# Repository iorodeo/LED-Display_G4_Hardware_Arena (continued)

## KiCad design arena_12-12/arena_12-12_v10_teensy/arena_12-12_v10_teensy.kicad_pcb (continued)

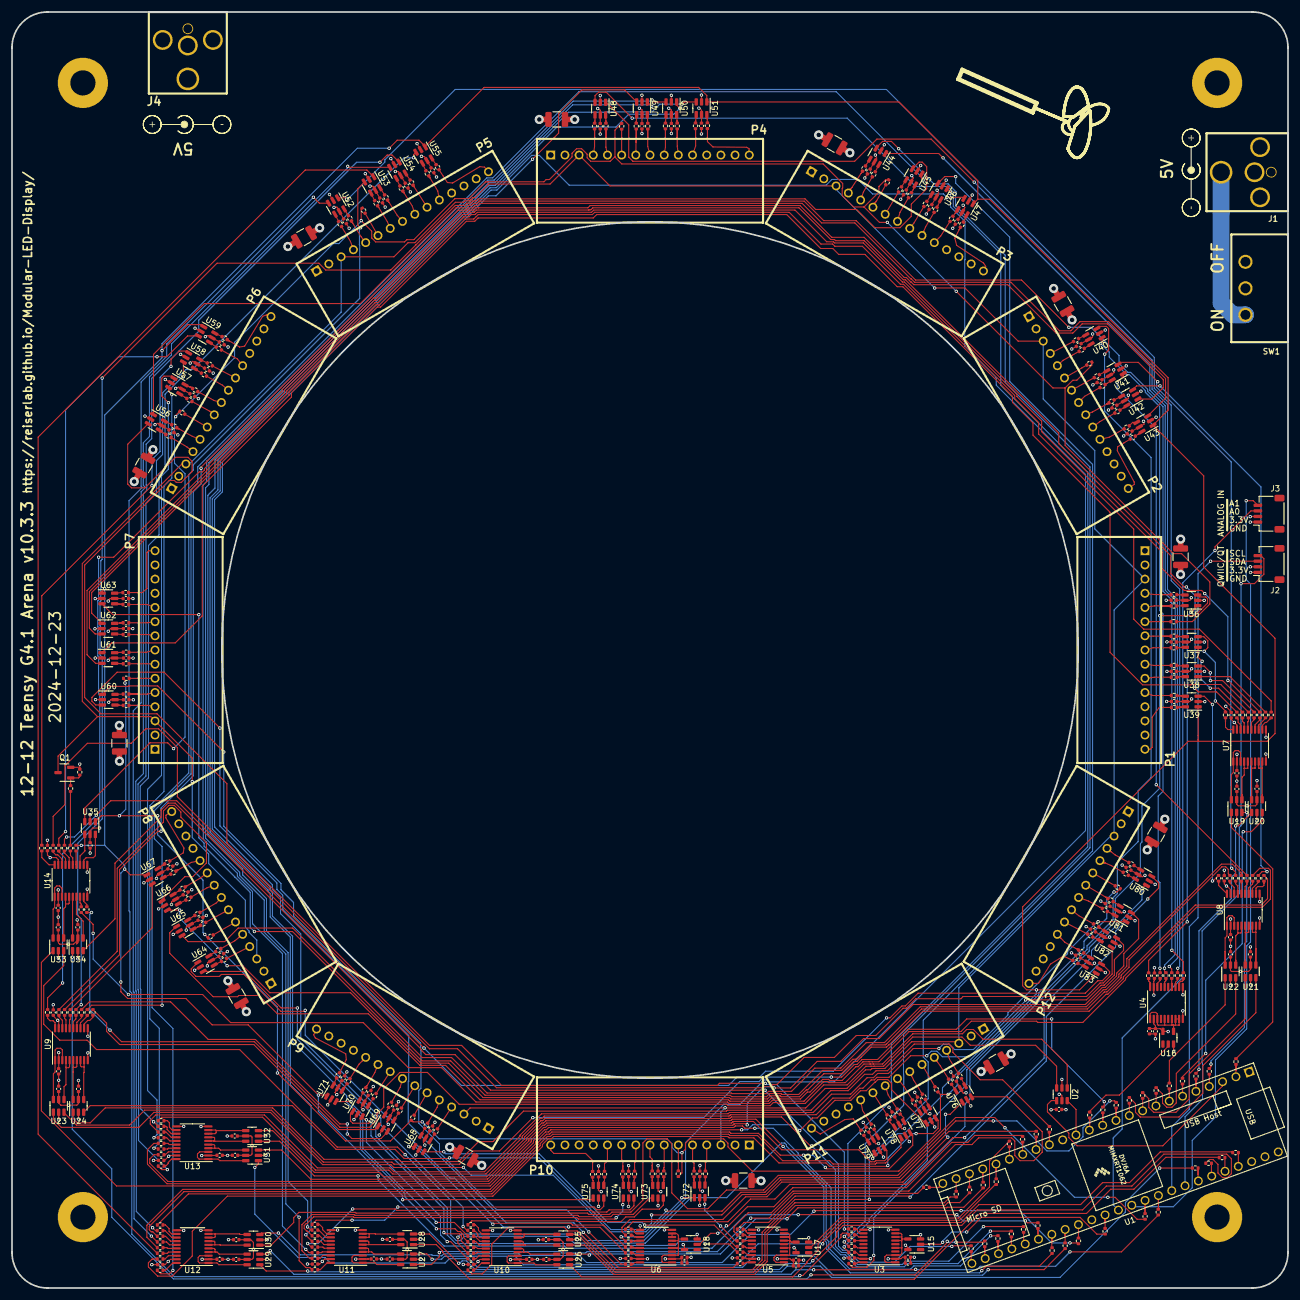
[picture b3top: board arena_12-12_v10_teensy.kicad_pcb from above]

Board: 6 copper layers, 228.6 x 228.6 mm, 445 parts (0 on the bottom side), 504 nets.

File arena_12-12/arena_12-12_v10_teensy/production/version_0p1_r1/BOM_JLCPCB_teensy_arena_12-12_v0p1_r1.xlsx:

Comment | Designator | Footprint | LCSC Part #（optional） | Qty
33 Ohm resistor | R215,R62,R48,R75,R201,R173,R177,R222,R214,R147,R10,R212,R203,R168,R139,R91,R86,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 | 0402 | C25105 | 232
0.1uF ceramic capacitor | C30,C67,C69,C48,C91,C5,C61,C26,C19,C39,C40,C76,C73,C2,C93,C60,C50,C25,C15,C46,C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 | 0402 | C1525 | 94
SN74LVC2G17DBVR dual Schmitt-trigger buffer | U36,U60,U33,U45,U20,U28,U2,U48,U38,U79,U62,U37,U63,U49,U26,U70,U76,U56,U53,U69,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 | SOT-23-6 | C10429 | 66
MOSFET N-channel | Q1 | SOT-23-3 | C165220 | 1
100uF ceramic capacitor | C97,C98,C106,C102,C99,C105,C95,C96,C100,C104,C103,C101 | 1210 | C7432790 | 12
Level shifter TXB0108PWR | U13,U6,U10,U3,U14,U4,U7,U12,U8,U9,U11,U5 | TSSOP-20 | C53406 | 12
4-Pin Connector, JST SM04B-SRSS-TB or similar | J2 ,J3 | SMD,P=1mm | C145956 | 2
SN74LVC1G17DBVR single schmitt trigger buffer | U17,U16,U15,U18 | SOT-23-5 | C7836 | 4
200 Ohm resistor | R1 | 0402 | C25087 | 1
20k Ohms resistor | R2 | 0402 | C25765 | 1
15x1 female header, 0.1in pitch | P10,P12,P7,P9,P11,P5,P4,P1,P6,P8,P2,P3 | through hole | global parts | 12
Slide Switch SPDT | SW1 | through hole | global parts | 1
DC Power Barrel Jack | J1, J4 | through hole | global parts | 2
Teensy4.1 | U1 | through hole | global parts | 1

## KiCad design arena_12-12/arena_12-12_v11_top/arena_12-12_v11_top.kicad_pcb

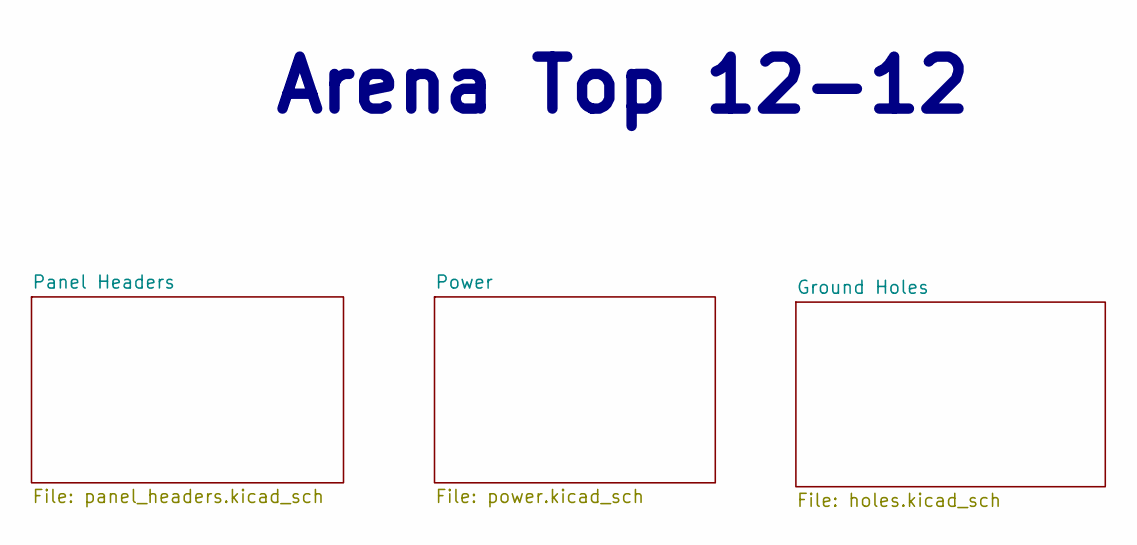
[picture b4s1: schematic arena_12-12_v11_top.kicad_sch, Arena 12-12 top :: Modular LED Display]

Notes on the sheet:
Arena Top 12-12

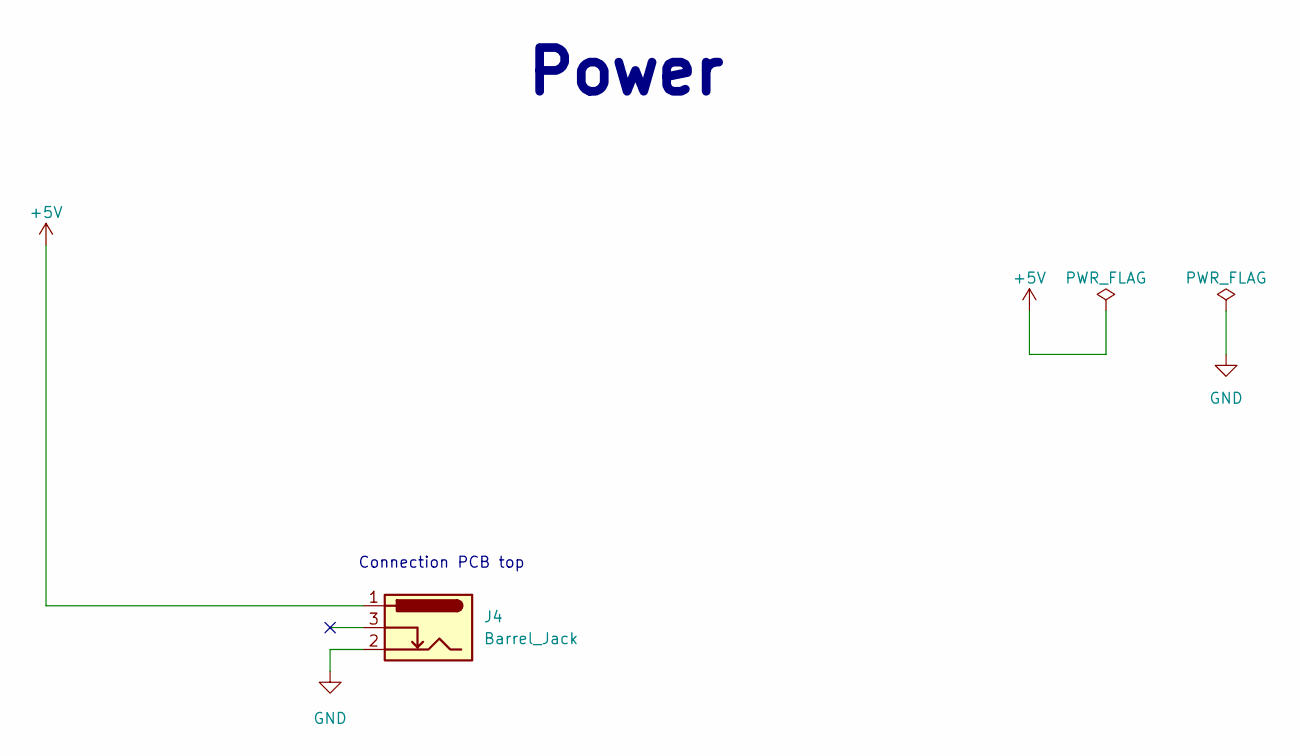
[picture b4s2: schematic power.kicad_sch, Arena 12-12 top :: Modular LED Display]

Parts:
J4: Barrel_Jack; BarrelJack_CUI_PJ-036AH-SMT_Horizontal; MPN PJ-036AH-SMT-TR; DigiKey PN CP-036AHPJTR-ND

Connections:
+5V: J4.1; also elsewhere on the board
GND: J4.2; also elsewhere on the board

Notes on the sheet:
Connection PCB top
Power

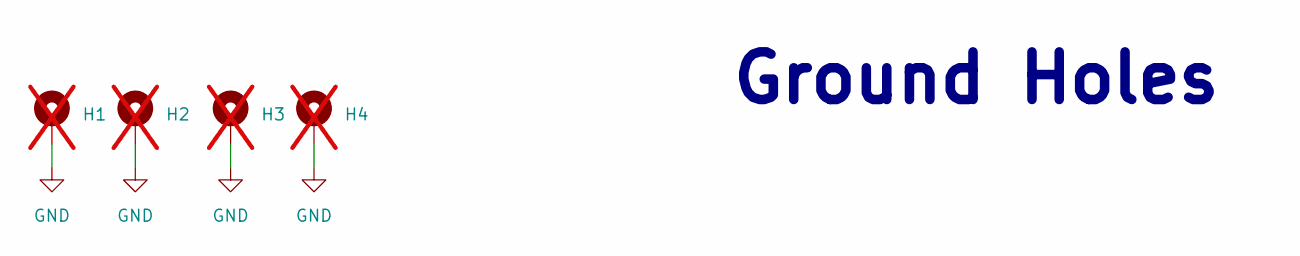
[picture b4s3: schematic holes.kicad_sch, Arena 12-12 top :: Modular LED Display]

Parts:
H1, H2, H3, H4: MountingHole_Pad; MountingHole_4.5mm_Pad; not fitted

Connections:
GND: H1.1, H2.1, H3.1, H4.1; also elsewhere on the board

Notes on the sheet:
Ground Holes

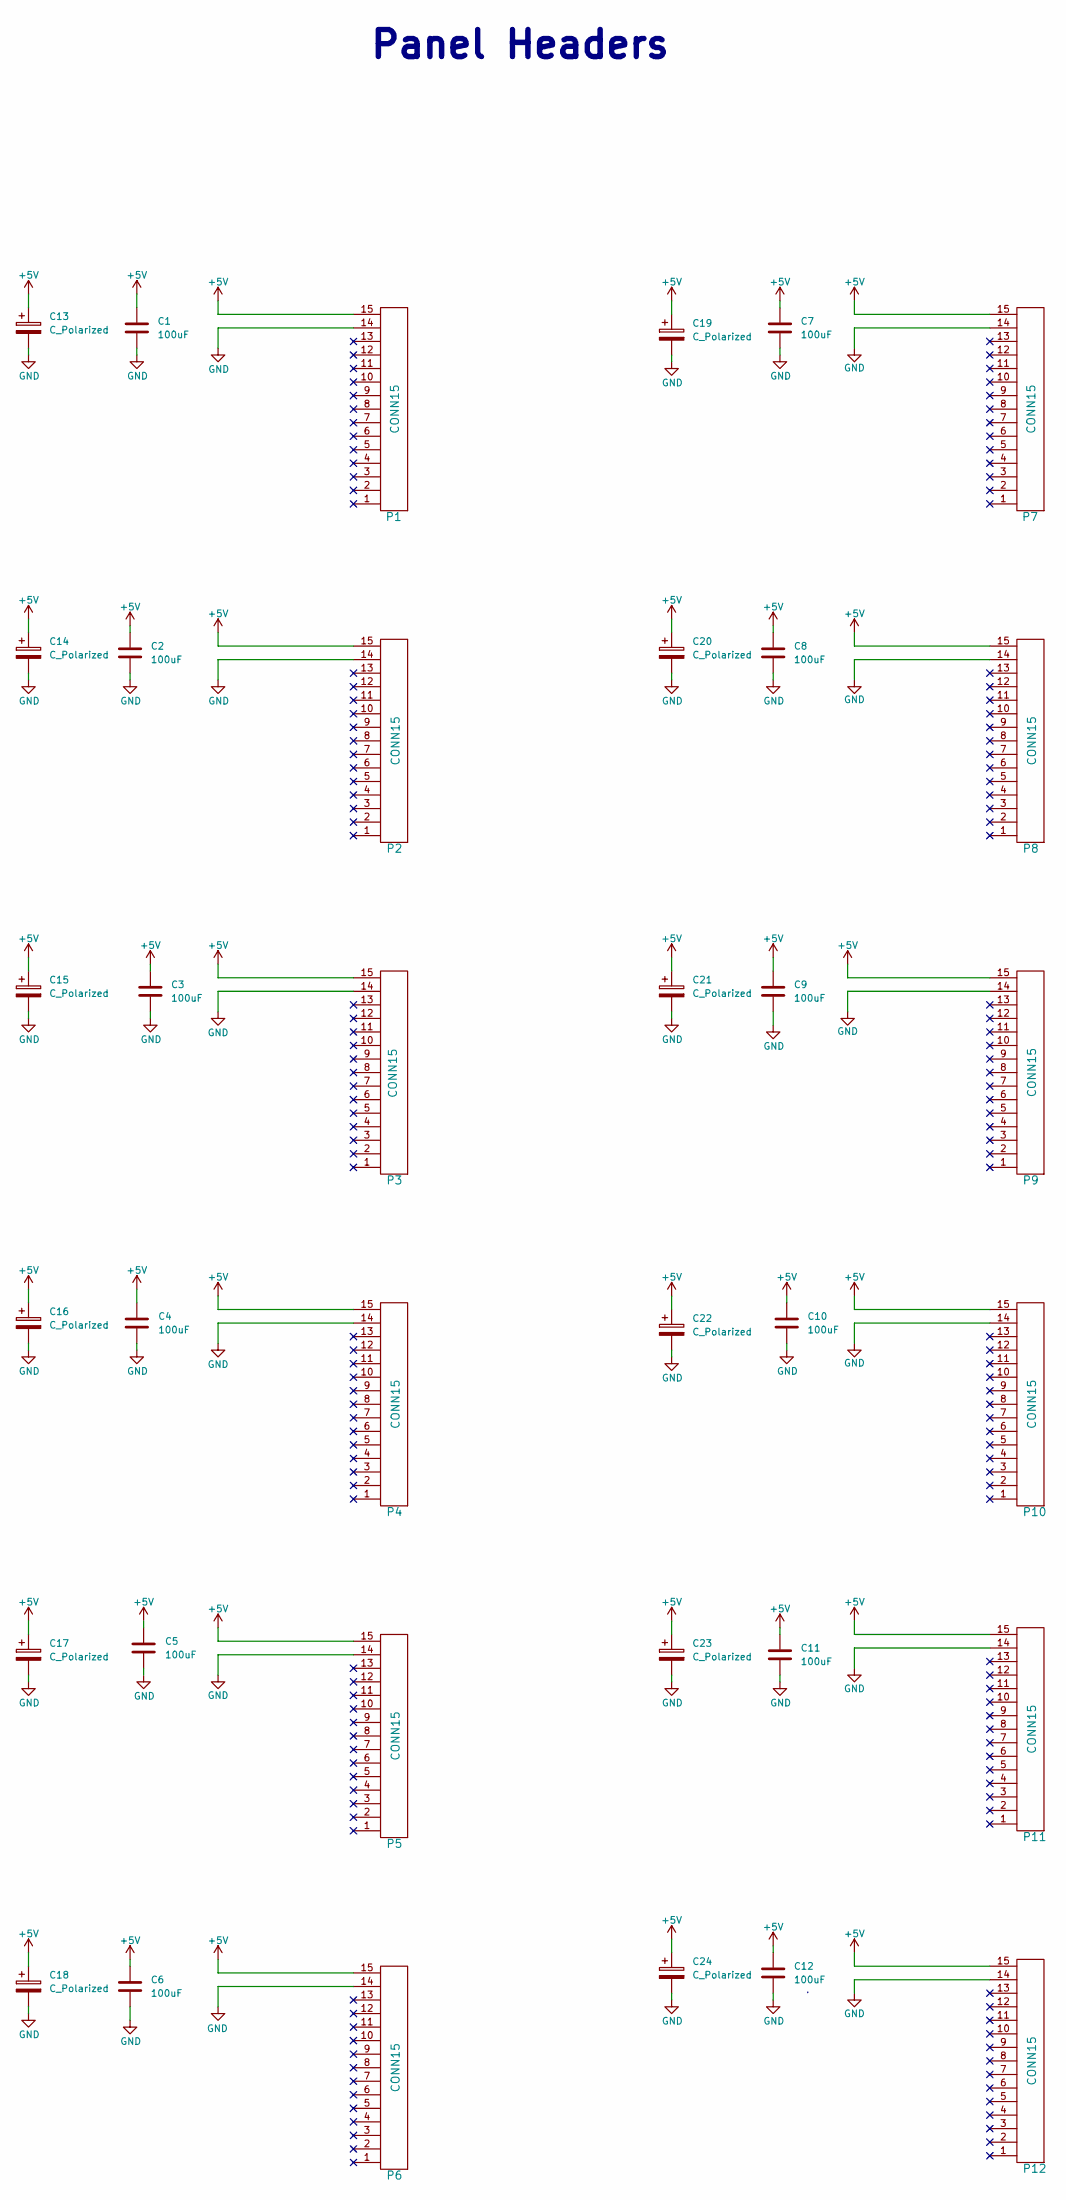
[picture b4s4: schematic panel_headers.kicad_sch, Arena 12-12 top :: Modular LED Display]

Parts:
C1, C2, C3, C4, C5, C6, C7, C8, C9, C10, C11, C12: 100uF; C_1210_3225Metric; MPN HGC1210R5107M160NSVK; LCSC Part # C7432790
C13, C14, C15, C16, C17, C18, C19, C20, C21, C22, C23, C24: C_Polarized; CP_Elec_6.3x7.7; MPN EEEFTH101XAP; DigiKey PN PCE5024TR-ND
P1, P2, P3, P4, P5, P6, P7, P8, P9, P10, P11, P12: CONN15; HEADER_TOP; MPN PRPC040SAAN-RC; DigiKey PN S1011EC-40-ND

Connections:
+5V: C1.1, C2.1, C3.1, C4.1, C5.1, C6.1, C7.1, C8.1, C9.1, C10.1, C11.1, C12.1, C13.1, C14.1, C15.1, C16.1, C17.1, C18.1, C19.1, C20.1, C21.1, C22.1, C23.1, C24.1, P1.15, P2.15, P3.15, P4.15, P5.15, P6.15, P7.15, P8.15, P9.15, P10.15, P11.15, P12.15; also elsewhere on the board
GND: C1.2, C2.2, C3.2, C4.2, C5.2, C6.2, C7.2, C8.2, C9.2, C10.2, C11.2, C12.2, C13.2, C14.2, C15.2, C16.2, C17.2, C18.2, C19.2, C20.2, C21.2, C22.2, C23.2, C24.2, P1.14, P2.14, P3.14, P4.14, P5.14, P6.14, P7.14, P8.14, P9.14, P10.14, P11.14, P12.14; also elsewhere on the board

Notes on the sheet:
Panel Headers

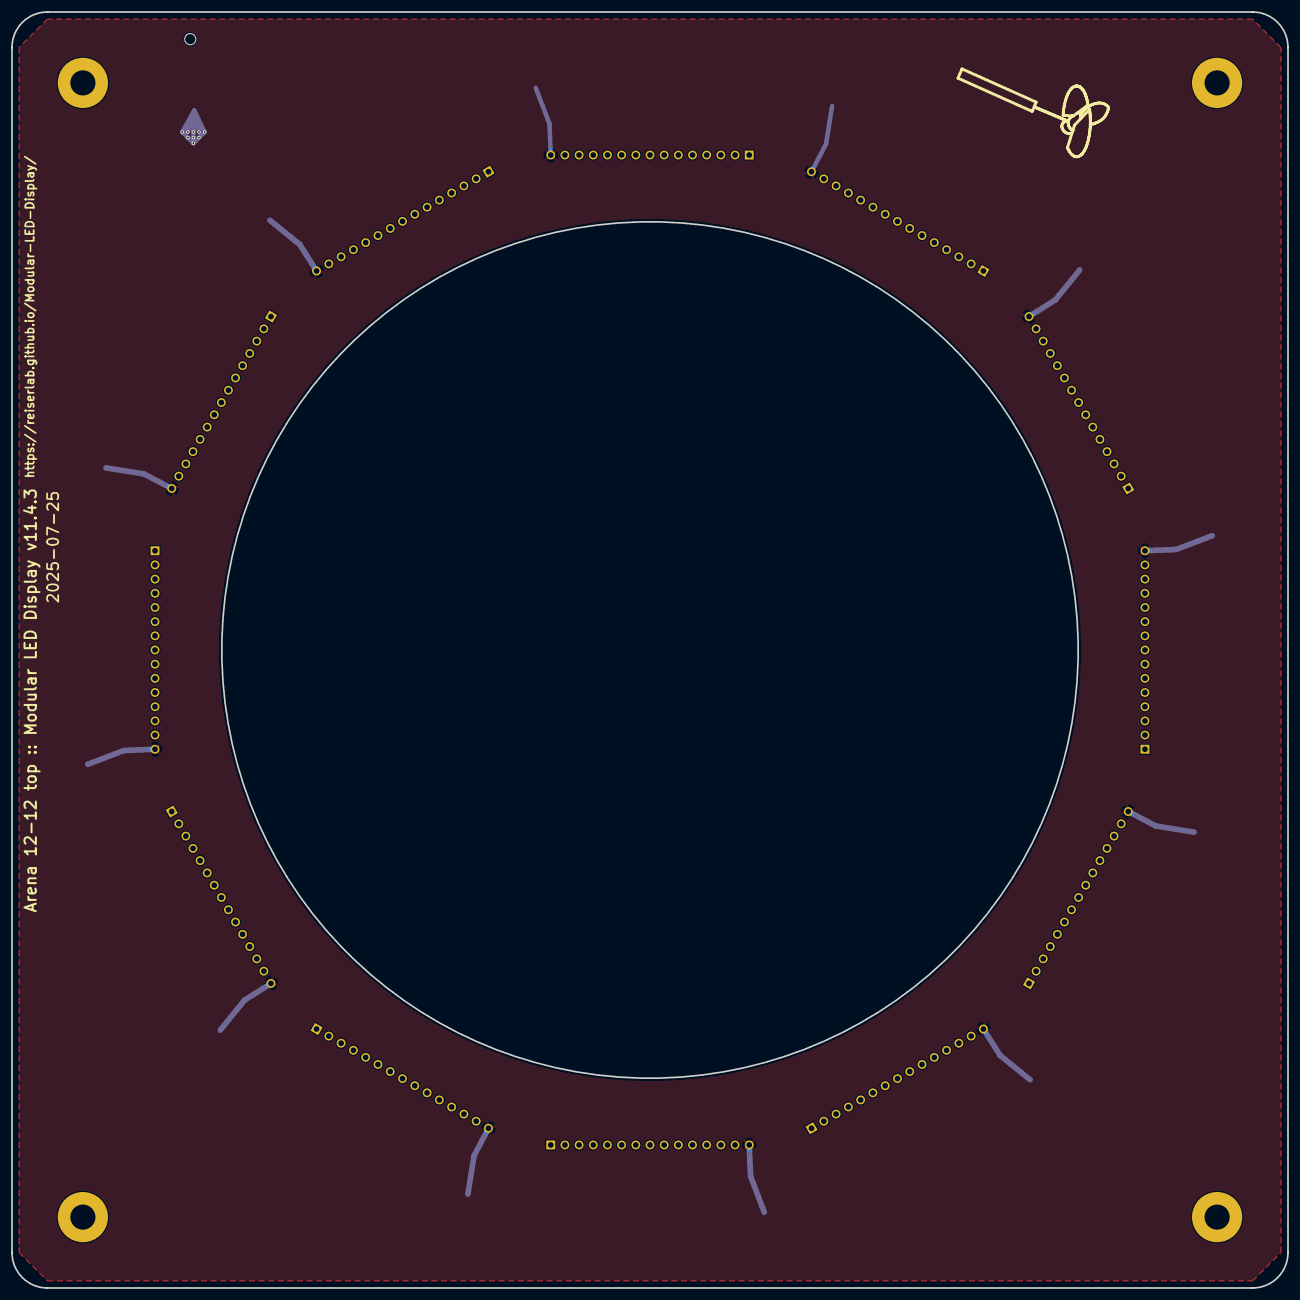
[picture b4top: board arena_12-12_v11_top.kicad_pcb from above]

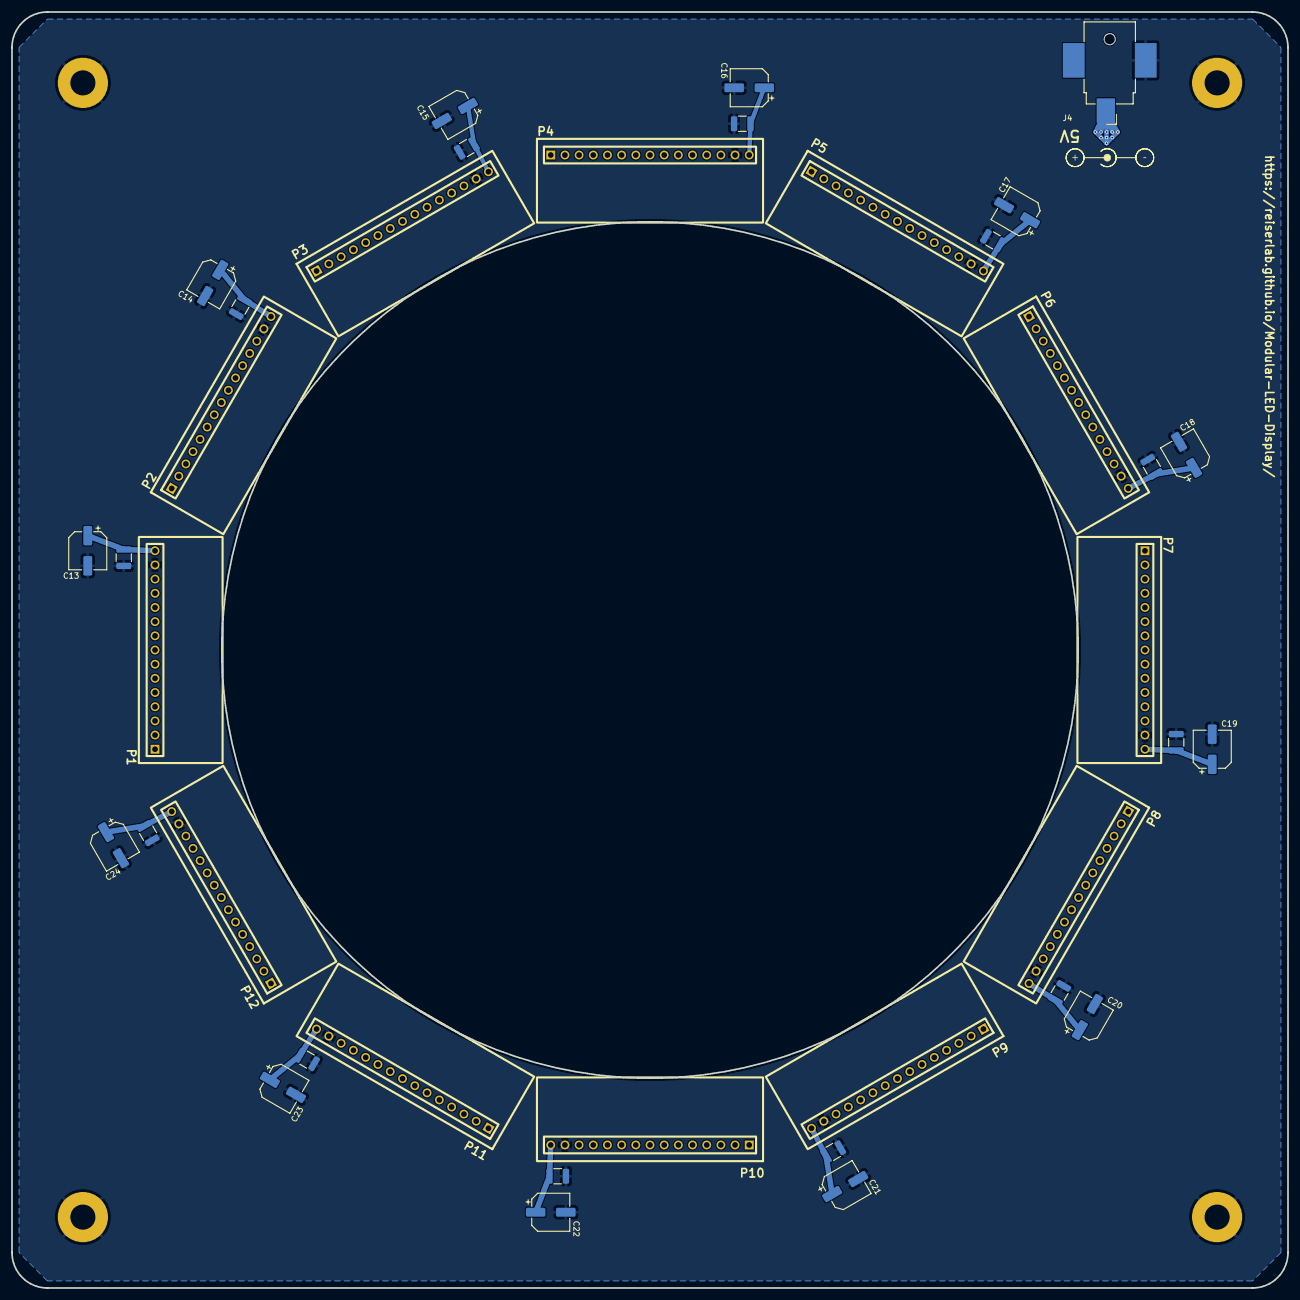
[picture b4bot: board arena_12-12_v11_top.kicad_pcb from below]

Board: 2 copper layers, 228.6 x 228.6 mm, 41 parts (37 on the bottom side), 2 nets.

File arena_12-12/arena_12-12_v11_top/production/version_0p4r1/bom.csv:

Designator,Footprint,Quantity,Value,LCSC Part #
"C1, C10, C11, C12, C2, C3, C4, C5, C6, C7, C8, C9",1210,12,100uF,C7432790
"C13, C14, C15, C16, C17, C18, C19, C20, C21, C22, C23, C24",CP_Elec_6.3x7.7,12,C_Polarized,C165974
J4,DCJACK_2PIN_HIGHCURRENT,1,Barrel_Jack,C2928097
"P1, P10, P11, P12, P2, P3, P4, P5, P6, P7, P8, P9",HEADER_TOP,12,CONN15,C7501269

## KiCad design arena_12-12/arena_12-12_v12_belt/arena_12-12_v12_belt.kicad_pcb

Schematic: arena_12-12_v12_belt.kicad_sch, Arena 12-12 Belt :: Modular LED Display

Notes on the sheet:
Arena 12-12 G4.1 Belt

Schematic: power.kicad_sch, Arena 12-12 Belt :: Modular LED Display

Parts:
J4: Barrel_Jack; BarrelJack_CUI_PJ-036AH-SMT_Horizontal; MPN PJ-036AH-SMT-TR; DigiKey PN CP-036AHPJTR-ND

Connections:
+5V: J4.1; also elsewhere on the board
GND: J4.2; also elsewhere on the board

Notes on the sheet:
Connection PCB top
Power

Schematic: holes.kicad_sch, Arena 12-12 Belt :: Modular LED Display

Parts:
H1, H2, H3, H4: MountingHole_Pad; MountingHole_4.5mm_Pad; not fitted

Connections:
GND: H1.1, H2.1, H3.1, H4.1; also elsewhere on the board

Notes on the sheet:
Ground Holes

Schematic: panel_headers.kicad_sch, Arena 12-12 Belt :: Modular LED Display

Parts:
C1, C2, C3, C4, C5, C6, C7, C8, C9, C10, C11, C12: 100uF; C_1210_3225Metric; MPN HGC1210R5107M160NSVK; LCSC Part # C7432790
C13, C14, C15, C16, C17, C18, C19, C20, C21, C22, C23, C24: C_Polarized; CP_Elec_6.3x7.7; MPN EEEFTH101XAP; DigiKey PN PCE5024TR-ND
P1, P2, P3, P4, P5, P6, P7, P8, P9, P10, P11, P12: CONN15; PinHeader_1x15_P2.54mm_Horizontal; MPN XDZ254-1-15-W-2.5-G1; DigiKey PN S1011EC-40-ND

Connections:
+5V: C1.1, C2.1, C3.1, C4.1, C5.1, C6.1, C7.1, C8.1, C9.1, C10.1, C11.1, C12.1, C13.1, C14.1, C15.1, C16.1, C17.1, C18.1, C19.1, C20.1, C21.1, C22.1, C23.1, C24.1, P1.1, P2.1, P3.1, P4.1, P5.1, P6.1, P7.1, P8.1, P9.1, P10.1, P11.1, P12.1; also elsewhere on the board
GND: C1.2, C2.2, C3.2, C4.2, C5.2, C6.2, C7.2, C8.2, C9.2, C10.2, C11.2, C12.2, C13.2, C14.2, C15.2, C16.2, C17.2, C18.2, C19.2, C20.2, C21.2, C22.2, C23.2, C24.2, P1.2, P2.2, P3.2, P4.2, P5.2, P6.2, P7.2, P8.2, P9.2, P10.2, P11.2, P12.2; also elsewhere on the board

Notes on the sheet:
Panel Headers

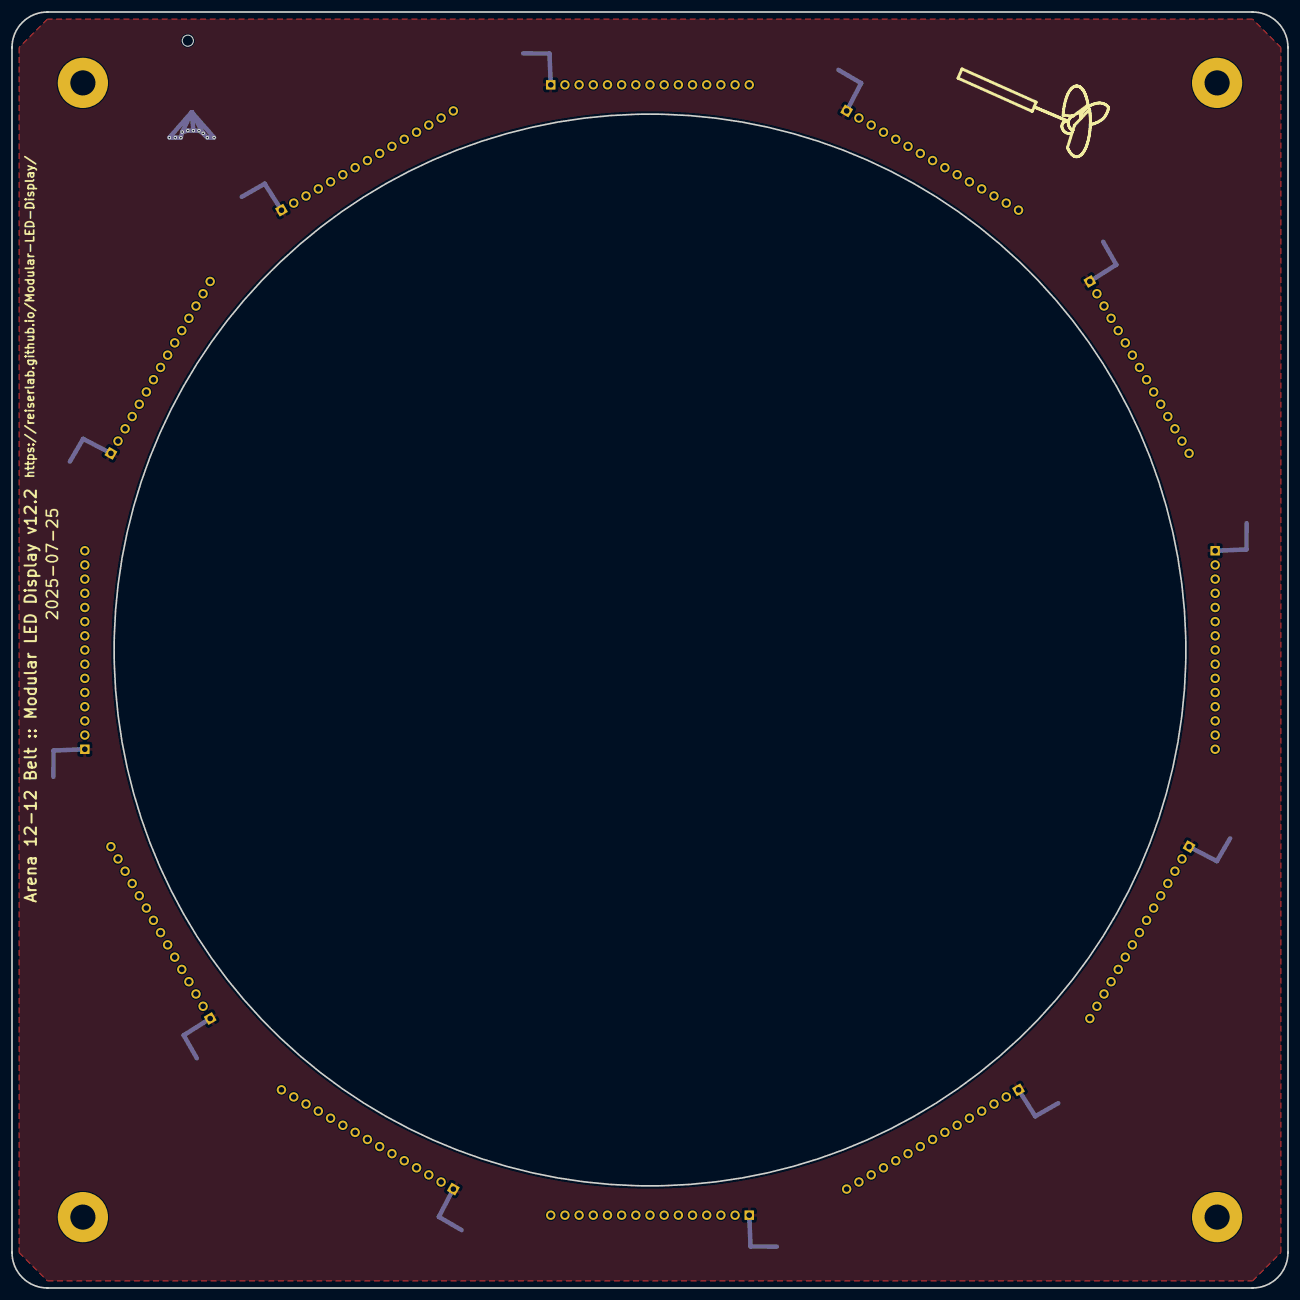
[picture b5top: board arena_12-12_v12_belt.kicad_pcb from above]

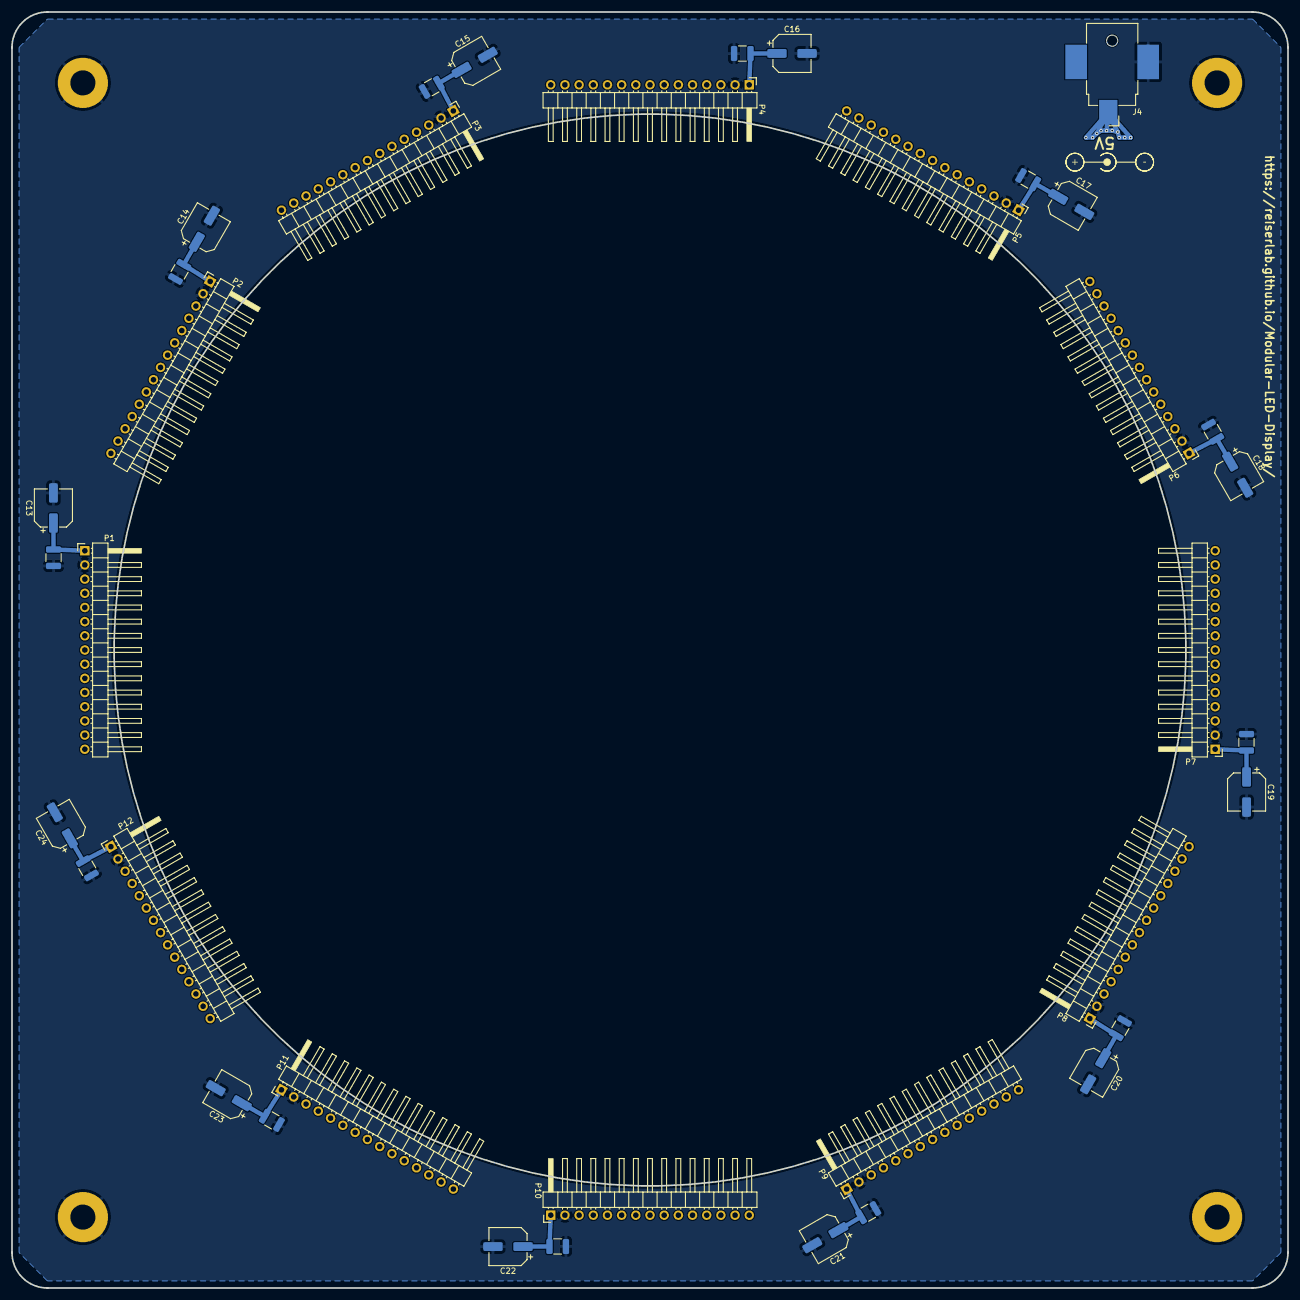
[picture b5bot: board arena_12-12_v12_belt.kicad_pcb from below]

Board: 2 copper layers, 228.6 x 228.6 mm, 41 parts (37 on the bottom side), 2 nets.

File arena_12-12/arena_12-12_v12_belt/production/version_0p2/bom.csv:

Designator,Footprint,Quantity,Value,LCSC Part #
"C1, C10, C11, C12, C2, C3, C4, C5, C6, C7, C8, C9",1210,12,100uF,C7432790
"C13, C14, C15, C16, C17, C18, C19, C20, C21, C22, C23, C24",CP_Elec_6.3x7.7,12,C_Polarized,C165974
J4,BarrelJack_CUI_PJ-036AH-SMT_Horizontal,1,Barrel_Jack,C3094052
"P1, P10, P11, P12, P2, P3, P4, P5, P6, P7, P8, P9",PinHeader_1x15_P2.54mm_Horizontal,12,CONN15,C18905875

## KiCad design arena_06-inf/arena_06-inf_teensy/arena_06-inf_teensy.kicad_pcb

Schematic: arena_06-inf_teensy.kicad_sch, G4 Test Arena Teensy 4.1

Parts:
C1, C2, C3, C4, C5, C6: C_Polarized_Small; Capacitor_Polarized
H1, H2, H3, H4: MountingHole_Pad; MountingHole_3.2mm_M3_DIN965_Pad
J1: Barrel_Jack; DCJACK_2PIN_HIGHCURRENT
J2, J3: Conn_01x04_Pin; NS-Tech_Grove_1x04_P2mm_Horizontal
P1, P2, P3, P4, P5, P6: CONN15; HEADER_TOP
Q2: MOSFET_NCHAN; SOT-23-3
R1: 200; R_0805_2012Metric
R2: 20k; R_0805_2012Metric
SW1: SW_SPDT; slide_switch
U1, U2, U3, U4, U5, U6: SPARKFUN_TXB0104
U7: Teensy4.1; Teensy41

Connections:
/3V3: J2.2, J3.2, U1.6 (LV), U2.6 (LV), U3.6 (LV), U4.6 (LV), U5.6 (LV), U6.6 (LV), U7.15 (3V3), U7.46 (3V3)
/5V: U1.9 (HV), U2.9 (HV), U3.9 (HV), U4.9 (HV), U5.9 (HV), U6.9 (HV), U7.48 (VIN), U7.49 (VUSB)
/A0: J3.3, U7.36 (14_A0_TX3_SPDIF_OUT)
/A1: J3.4, U7.37 (15_A1_RX3_SPDIF_IN)
/CS_00_3V3: U3.2 (A1), U7.5 (3_LRCLK2)
/CS_00_5V: P1.7, P4.7, U3.13 (B1)
/CS_01_3V3: U3.3 (A2), U7.6 (4_BCLK2)
/CS_01_5V: P1.8, P4.8, U3.12 (B2)
/CS_02_3V3: U3.4 (A3), U7.7 (5_IN2)
/CS_02_5V: P1.9, P4.9, U3.11 (B3)
/CS_03_3V3: U3.5 (A4), U7.8 (6_OUT1D)
/CS_03_5V: P1.10, P4.10, U3.10 (B4)
/CS_04_3V3: U4.2 (A1), U7.9 (7_RX2_OUT1A)
/CS_04_5V: P1.11, P4.11, U4.13 (B1)
/CS_05_3V3: U4.3 (A2), U7.10 (8_TX2_IN1)
/CS_05_5V: P2.7, P5.7, U4.12 (B2)
/CS_06_3V3: U4.4 (A3), U7.11 (9_OUT1C)
/CS_06_5V: P2.8, P5.8, U4.11 (B3)
/CS_07_3V3: U4.5 (A4), U7.21 (29_TX7)
/CS_07_5V: P2.9, P5.9, U4.10 (B4)
/CS_08_3V3: U5.2 (A1), U7.22 (30_CRX3)
/CS_08_5V: P2.10, P5.10, U5.13 (B1)
/CS_09_3V3: U5.3 (A2), U7.23 (31_CTX3)
/CS_09_5V: P2.11, P5.11, U5.12 (B2)
/CS_10_3V3: U5.4 (A3), U7.24 (32_OUT1B)
/CS_10_5V: P3.7, P6.7, U5.11 (B3)
/CS_11_3V3: U5.5 (A4), U7.25 (33_MCLK2)
/CS_11_5V: P3.8, P6.8, U5.10 (B4)
/CS_12_3V3: U6.2 (A1), U7.26 (34_RX8)
/CS_12_5V: P3.9, P6.9, U6.13 (B1)
/CS_13_3V3: U6.3 (A2), U7.27 (35_TX8)
/CS_13_5V: P3.10, P6.10, U6.12 (B2)
/CS_14_3V3: U6.4 (A3), U7.28 (36_CS)
/CS_14_5V: P3.11, P6.11, U6.11 (B3)
/EXT_INT_5V: P1.15, P2.15, P3.15, P4.15, P5.15, P6.15
/MISO_0_3V3: U1.4 (A3), U7.14 (12_MISO_MQSL)
/MISO_0_5V: P1.6, P2.6, P3.6, U1.11 (B3)
/MISO_1_3V3: U2.4 (A3), U7.3 (1_TX1_CTX2_MISO1)
/MISO_1_5V: P4.6, P5.6, P6.6, U2.11 (B3)
/MOSI_0_3V3: U1.3 (A2), U7.13 (11_MOSI_CTX1)
/MOSI_0_5V: P1.5, P2.5, P3.5, U1.12 (B2)
/MOSI_1_3V3: U2.3 (A2), U7.18 (26_A12_MOSI1)
/MOSI_1_5V: P4.5, P5.5, P6.5, U2.12 (B2)
/RESET: R1.2, U7.29 (37_CS)
/RESET_PAN: P1.3, P2.3, P3.3, P4.3, P5.3, P6.3, Q2.3 (D)
/SCK_0_3V3: U1.2 (A1), U7.35 (13_SCK_LED)
/SCK_0_5V: P1.4, P2.4, P3.4, U1.13 (B1)
/SCK_1_3V3: U2.2 (A1), U7.19 (27_A13_SCK1)
/SCK_1_5V: P4.4, P5.4, P6.4, U2.13 (B1)
/SCL: J2.4, U7.41 (19_A5_SCL)
/SDA: J2.3, U7.40 (18_A4_SDA)
/VIN: C1.1, C2.1, C3.1, C4.1, C5.1, C6.1, P1.1, P2.1, P3.1, P4.1, P5.1, P6.1, SW1.2 (B)
/VIN_SW: J1.1, SW1.1 (A)
GND: C1.2, C2.2, C3.2, C4.2, C5.2, C6.2, H1.1, H2.1, H3.1, H4.1, J1.2, J2.1, J3.1, P1.2, P2.2, P3.2, P4.2, P5.2, P6.2, Q2.2 (S), R2.1, SW1.3 (C), U1.7 (GND), U1.8 (GND), U2.7 (GND), U2.8 (GND), U3.7 (GND), U3.8 (GND), U4.7 (GND), U4.8 (GND), U5.7 (GND), U5.8 (GND), U6.7 (GND), U6.8 (GND), U7.1 (GND), U7.34 (GND), U7.47 (GND)
unnamed: Q2.1 (G), R1.1, R2.2

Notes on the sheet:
SI2302-TP (Digikey SI2302-TPMSCT-ND)
Analog inputs
Level Shifters
Panel Headers
Power filtering
I2C connections for analog outputs, sensors etc.
7.5V to 9V
Reset Sink

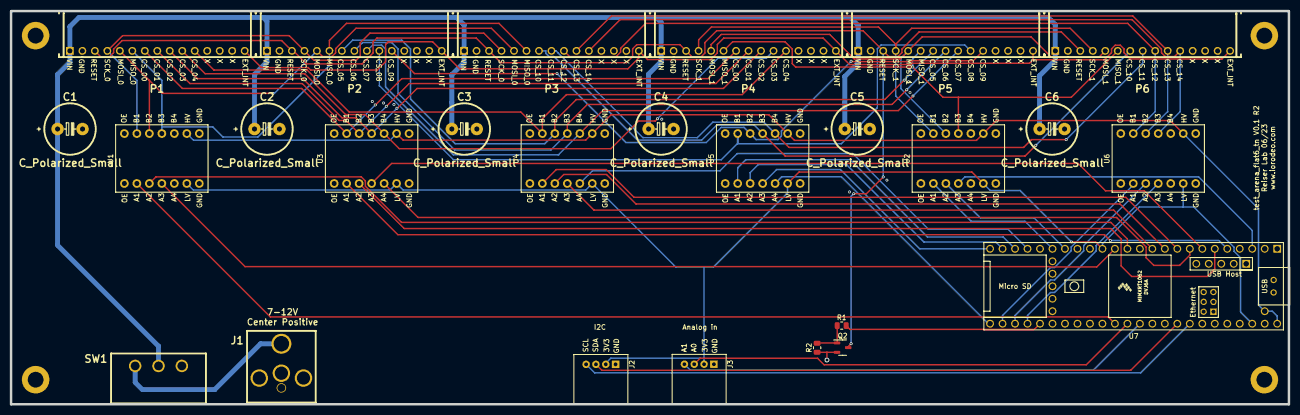
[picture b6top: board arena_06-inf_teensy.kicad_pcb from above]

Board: 4 copper layers, 260.0 x 80.0 mm, 30 parts (0 on the bottom side), 55 nets.

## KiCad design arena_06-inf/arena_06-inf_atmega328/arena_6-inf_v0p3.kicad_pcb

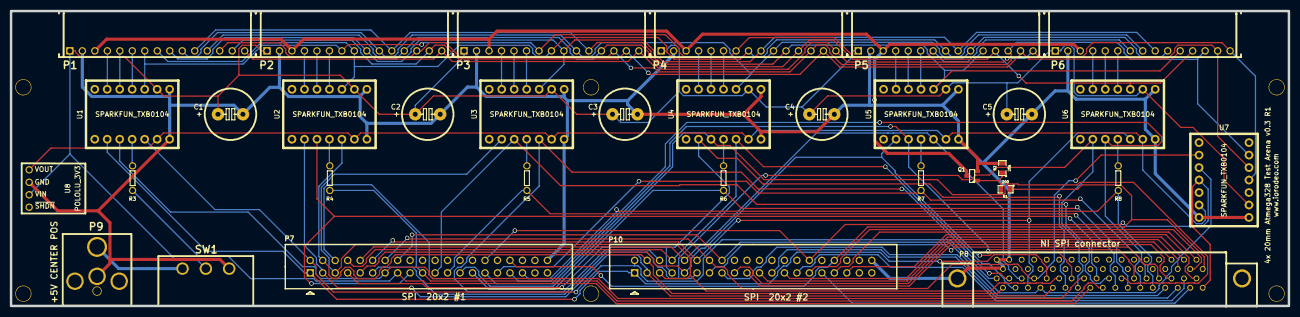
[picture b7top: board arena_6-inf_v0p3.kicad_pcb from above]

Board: 2 copper layers, 260.0 x 60.0 mm, 39 parts (0 on the bottom side), 79 nets.

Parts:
C1, C2, C3, C4, C5: 10uF; Capacitor_Polarized
M1, M2, M3, M4, M5, M6: VAL**; MOUNT_HOLE_4_40
P1, P2, P3, P4, P5, P6: CONN15; HEADER_TOP
P7, P10: CONN_20X2; PIN_ARRAY_SHRD_20X2
P8: CONN_34X2; TE_CONN_DSUB_RA_68
P9: CONN_2; DCJACK_2PIN_HIGHCURRENT
Q1: MOSFET_NCHAN; SOT23
R1: 200; SM0805
R2: 20k; SM0805
R3, R4, R5, R6, R7, R8: R; R_SMALL
SW1: SWITCH_INV; slide_switch
U1, U2, U3, U4, U5, U6, U7: SPARKFUN_TXB0104
U8: POLOLU_3V3

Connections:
+5V: P9.1, SW1.1
/3V3: U1.6, U2.6, U3.6, U4.6, U5.6, U6.6, U7.6, U8.4
/5V: C1.1, C2.1, C3.1, C4.1, C5.1, P1.1, P2.1, P3.1, P4.1, P5.1, P6.1, SW1.2, U1.9, U2.9, U3.9, U4.9, U5.9, U6.9, U7.9, U8.2
/CS_0_3V3: P7.2, P8.35, P10.2, U1.5
/CS_0_5V: P1.7, P2.7, P3.7, P4.7, P5.7, P6.7, U1.10
/CS_1_3V3: P7.4, P8.36, P10.4, U2.5
/CS_1_5V: P1.8, P2.8, P3.8, P4.8, P5.8, P6.8, U2.10
/CS_2_3V3: P7.6, P8.37, P10.6, U3.5
/CS_2_5V: P1.9, P2.9, P3.9, P4.9, P5.9, P6.9, U3.10
/CS_3_3V3: P7.8, P8.38, P10.8, U4.5
/CS_3_5V: P1.10, P2.10, P3.10, P4.10, P5.10, P6.10, U4.10
/CS_4_3V3: P7.10, P8.39, P10.10, U5.5
/CS_4_5V: P1.11, P2.11, P3.11, P4.11, P5.11, P6.11, U5.10
/CS_5_3V3: P7.12, P8.40, P10.12, U6.5
/CS_5_5V: P1.12, P2.12, P3.12, P4.12, P5.12, P6.12, U6.10
/CS_6_3V3: P7.14, P8.41, P10.14, U7.2
/CS_6_5V: P1.13, P2.13, P3.13, P4.13, P5.13, P6.13, U7.13
/CS_7_3V3: P7.16, P8.42, P10.16, U7.3
/CS_7_5V: P1.14, P2.14, P3.14, P4.14, P5.14, P6.14, U7.12
/EXT_INT_3V3: P7.30, P8.68, P10.30, U7.4
/EXT_INT_5V: P1.15, P2.15, P3.15, P4.15, P5.15, P6.15, U7.11
/MISO_0_3V3: P7.15, P8.50, R3.2
/MISO_0_5V: P1.6, U1.11
/MISO_1_3V3: P7.19, P8.52, R4.2
/MISO_1_5V: P2.6, U2.11
/MISO_2_3V3: P7.23, P8.54, R5.2
/MISO_2_5V: P3.6, U3.11
/MISO_3_3V3: P7.27, P8.56, R6.2
/MISO_3_5V: P4.6, U4.11
/MISO_4_3V3: P7.31, P8.58, R7.2
/MISO_4_5V: P5.6, U5.11
/MISO_5_3V3: P7.35, P8.60, R8.2
/MISO_5_5V: P6.6, U6.11
/MISO_6_3V3: P8.62, P10.15
/MISO_7_3V3: P8.63, P10.19
/MISO_8_3V3: P8.64, P10.23
/MISO_9_3V3: P8.65, P10.27
/MISO_10_3V3: P8.66, P10.31
/MISO_11_3V3: P8.67, P10.35
/MOSI_0_3V3: P7.13, P8.49, U1.3
/MOSI_0_5V: P1.5, U1.12
/MOSI_1_3V3: P7.17, P8.51, U2.3
/MOSI_1_5V: P2.5, U2.12
/MOSI_2_3V3: P7.21, P8.53, U3.3
/MOSI_2_5V: P3.5, U3.12
/MOSI_3_3V3: P7.25, P8.55, U4.3
/MOSI_3_5V: P4.5, U4.12
/MOSI_4_3V3: P7.29, P8.57, U5.3
/MOSI_4_5V: P5.5, U5.12
/MOSI_5_3V3: P7.33, P8.59, U6.3
/MOSI_5_5V: P6.5, U6.12
/MOSI_6_3V3: P8.61, P10.13
/MOSI_7_3V3: P8.29, P10.17
/MOSI_8_3V3: P8.30, P10.21
/MOSI_9_3V3: P8.31, P10.25
/MOSI_10_3V3: P8.32, P10.29
/MOSI_11_3V3: P8.33, P10.33
/RESET: P7.34, P8.34, P10.34, R1.1
/RESET_PAN: P1.3, P2.3, P3.3, P4.3, P5.3, P6.3, Q1.3
/SCK_0_3V3: P7.1, P8.43, P10.1, U1.2
/SCK_0_5V: P1.4, U1.13
/SCK_1_3V3: P7.3, P8.44, P10.3, U2.2
/SCK_1_5V: P2.4, U2.13
/SCK_2_3V3: P7.5, P8.45, P10.5, U3.2
/SCK_2_5V: P3.4, U3.13
/SCK_3_3V3: P7.7, P8.46, P10.7, U4.2
/SCK_3_5V: P4.4, U4.13
/SCK_4_3V3: P7.9, P8.47, P10.9, U5.2
/SCK_4_5V: P5.4, U5.13
/SCK_5_3V3: P7.11, P8.48, P10.11, U6.2
/SCK_5_5V: P6.4, U6.13
GND: C1.2, C2.2, C3.2, C4.2, C5.2, P1.2, P2.2, P3.2, P4.2, P5.2, P6.2, P7.40, P8.1, P8.2, P8.3, P8.69, P9.2, P10.40, Q1.2, R2.2, SW1.3, U1.7, U1.8, U2.7, U2.8, U3.7, U3.8, U4.7, U4.8, U5.7, U5.8, U6.7, U6.8, U7.7, U7.8, U8.3
unnamed: Q1.1, R1.2, R2.1
unnamed: R3.1, U1.4
unnamed: R8.1, U6.4
unnamed: R6.1, U4.4
unnamed: R7.1, U5.4
unnamed: R4.1, U2.4
unnamed: R5.1, U3.4
